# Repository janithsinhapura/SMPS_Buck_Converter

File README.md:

# This is the SMPS Buck Converter PCB design made with KiCad

+ Input Voltage 5-40V
+ Nominal Output Volatage 3.3V
+ Maximum Load Current 500mA

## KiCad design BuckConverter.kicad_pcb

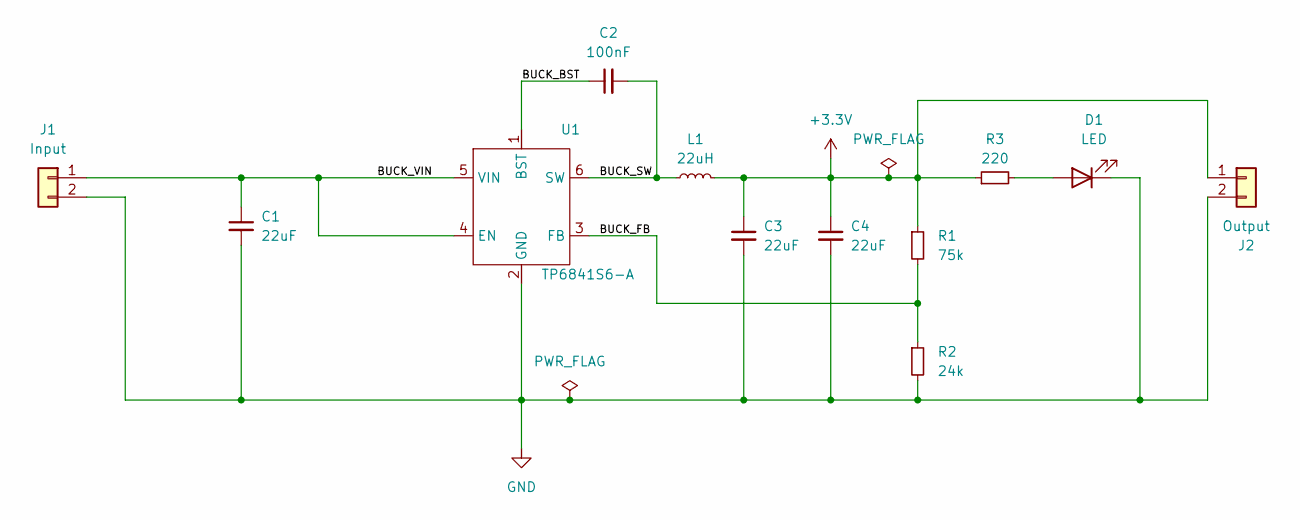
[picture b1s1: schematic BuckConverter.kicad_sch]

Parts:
C1, C3, C4: 22uF; C_1210_3225Metric
C2: 100nF; C_0603_1608Metric
D1: LED; LED_0603_1608Metric
J1: Input; PinHeader_1x02_P2.54mm_Vertical
J2: Output; PinHeader_1x02_P2.54mm_Vertical
L1: 22uH; NRS4018_TAY_inductor
R1: 75k; R_0603_1608Metric
R2: 24k; R_0603_1608Metric
R3: 220; R_0603_1608Metric
U1: TP6841S6-A; SOT-23-6

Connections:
+3.3V: C3.1, C4.1, J2.1, L1.2, R1.1, R3.1
/BUCK_BST: C2.1, U1.1 (BST)
/BUCK_FB: R1.2, R2.1, U1.3 (FB)
/BUCK_SW: C2.2, L1.1, U1.6 (SW)
/BUCK_VIN: C1.1, J1.1, U1.4 (EN), U1.5 (VIN)
GND: C1.2, C3.2, C4.2, D1.1 (K), J1.2, J2.2, R2.2, U1.2 (GND)
unnamed: D1.2 (A), R3.2

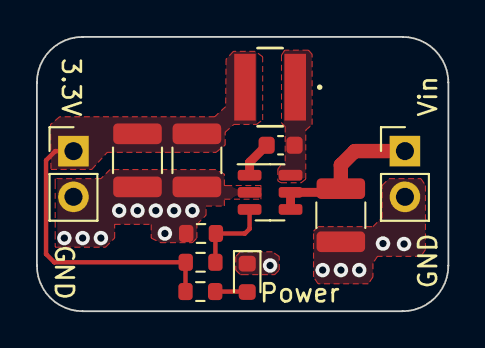
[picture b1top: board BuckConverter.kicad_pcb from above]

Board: 2 copper layers, 22.9 x 15.2 mm, 12 parts (0 on the bottom side), 7 nets.

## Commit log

2024-02-29 Add PCB project
2024-02-29 Add PCB Layout Image
